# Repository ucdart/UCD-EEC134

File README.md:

EEC 134 Design of High Frequency Systems
======

The EEC 134 course was created to satisfy the need for a senior project course for students who are interested in high freqeuency electronic systems. The two-quarter long course emphasizes on system level design concepts and strives to provide a hands-on experience. As the course evolves, the projects start to encompass many facets of electrical engineering, including system engineering, antenna design, analog circuit design, embedded systems, and digital signal processing. 

The first project option we have implemented is a frequency modulated continuous wave (FMCW) radar system that can perform range, Doppler, and synthetic aperture radar (SAR) measurements. In the first quarter, the students build an FMCW radar system using breadboard and off-the-shelf connectorized RF components. In the second quarter the students focus on improving the system performance and gauge their success by a performance competition. In the future, other project options, such as software-defined radio (SDR), RFID systems, wireless sensors networks, and RF/microwave biomedical systems, will be explored.

<div align="center">
<strong>Watch a live demo at the 2015 Bay Area Maker Faire:</strong><br>

<br>
</div>

----
This Github repo is used to distribute the EEC 134 lecture notes, lab manuals, and supplementary materials such as computer codes with registered EEC 134 students as well as anyone who is interested in the course materials. The public nature of this git repo means that that anyone can contribute to the development of the course materials. Simply create a [pull request](https://help.github.com/articles/using-pull-requests/)

----
Roadmap:
- Lab 1 Baseband circuits
 - add an ADC lab (far future)
 - bring back the function generator
- Lab 2 Amplifier:
 - design a lab for measuring the noise figure
- Lab 3 Oscillator:
 - add a lab on measuring phase noise after we buy new spectrum analyzers
 - add a lab on building a PLL
 - design a lab to demonstrate locking bewteen oscillators. Perhpas with two oscillators and a coupler? 
- Lab 4 Mixer：add modulation to this lab
 - design a lab to demonstrate IQ modulation & demodulation; use an attenuator to show the effect of IQ amplitude imbalance
- Lab 6 convert to a radar only lab 
 - add lab on comparing the sky, sun, and ground noise
- Lab 7 (new) design a comm system only lab
 - 
- PCB tutorial
 - update the screenshots with the OpenGL display option
 - add PCB assembly tutorial
 - add

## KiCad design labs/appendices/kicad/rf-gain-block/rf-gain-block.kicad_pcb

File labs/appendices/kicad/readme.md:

The "short-tline-wrk" is an ADS2013 workspace folder folder that contains the simulation setup and result for short-tline-gamma.pdf

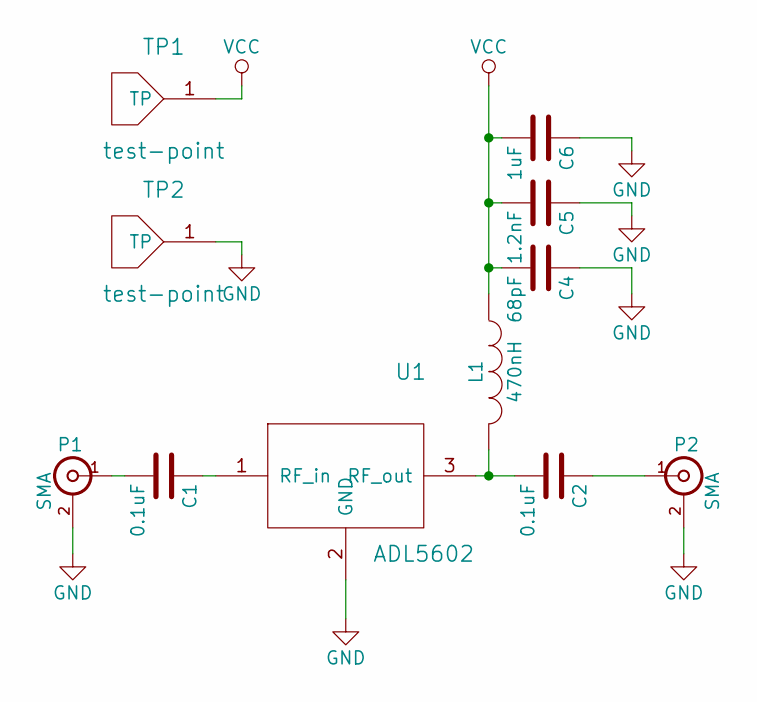
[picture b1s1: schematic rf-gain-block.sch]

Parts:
C1, C2: 0.1uF; smd_0603
C4: 68pF; smd_0603
C5: 1.2nF; smd_0603
C6: 1uF; smd_0603
L1: 470nH; cc_0603ls
P1, P2: SMA
TP1, TP2: test-point; tp
U1: ADL5602; adl5602

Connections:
GND: C4.1, C5.1, C6.1, P1.2 (Ext), P2.2 (Ext), TP2.1, U1.2 (GND)
unnamed: C1.1, U1.1 (RF_in)
unnamed: C1.2, P1.1 (In)
unnamed: C2.1, P2.1 (In)
unnamed: C2.2, L1.2, U1.3 (RF_out)
VCC: C4.2, C5.2, C6.2, L1.1, TP1.1

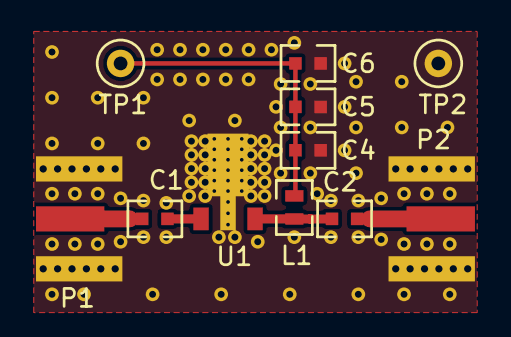
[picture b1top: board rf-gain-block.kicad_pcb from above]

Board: 2 copper layers, 11 parts (0 on the bottom side), 6 nets.

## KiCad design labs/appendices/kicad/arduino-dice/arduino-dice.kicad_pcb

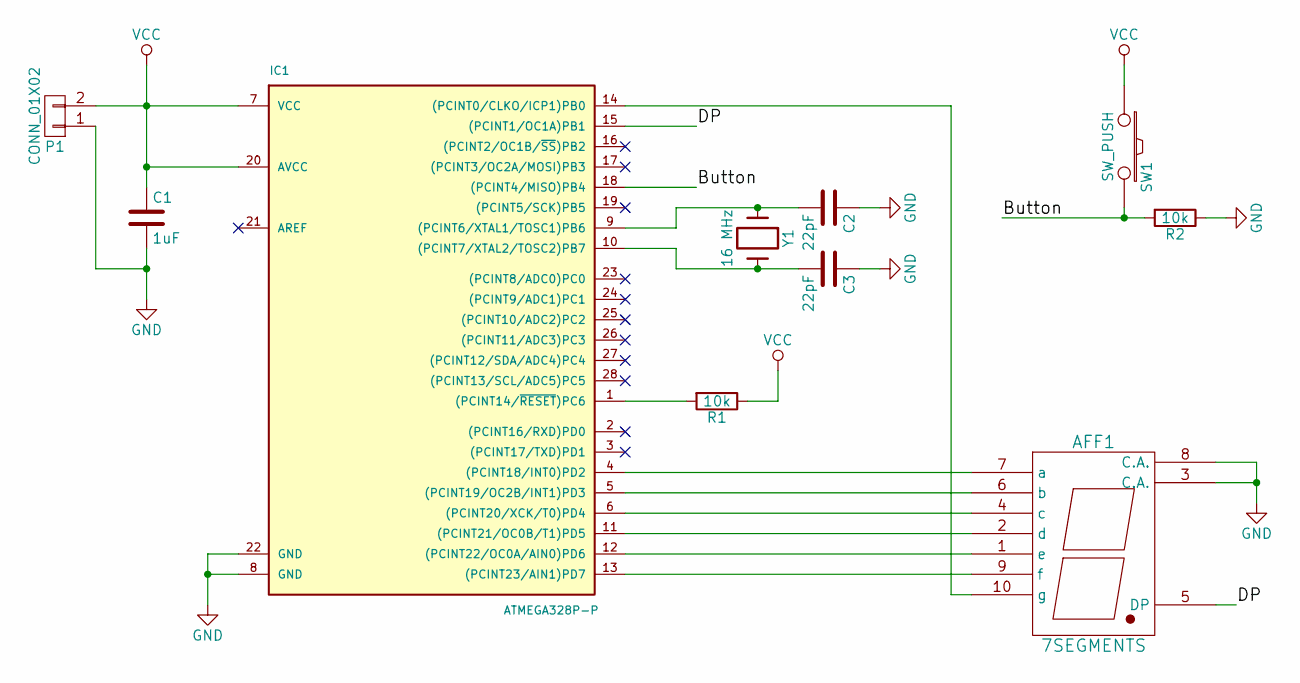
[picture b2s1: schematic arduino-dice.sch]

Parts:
AFF1: 7SEGMENTS; 7segment-hdsp-313e
C1: 1uF; smd_0603
C2, C3: 22pF; smd_0603
IC1: ATMEGA328P-P; atmega328p-pu
P1: CONN_01X02; Pin_Header_Straight_1x02
R1, R2: 10k; smd_0603
SW1: SW_PUSH; sw_push_b3f_1000
Y1: 16 MHz; crystal_hc49us

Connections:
/Button: IC1.18 ((PCINT4/MISO)PB4), R2.2, SW1.2
/DP: AFF1.5 (DP), IC1.15 ((PCINT1/OC1A)PB1)
GND: AFF1.3 (C.A.), AFF1.8 (C.A.), C1.2, C2.1, C3.1, IC1.8 (GND), IC1.22 (GND), P1.1, R2.1
unnamed: AFF1.1 (e), IC1.12 ((PCINT22/OC0A/AIN0)PD6)
unnamed: AFF1.2 (d), IC1.11 ((PCINT21/OC0B/T1)PD5)
unnamed: AFF1.4 (c), IC1.6 ((PCINT20/XCK/T0)PD4)
unnamed: AFF1.6 (b), IC1.5 ((PCINT19/OC2B/INT1)PD3)
unnamed: AFF1.7 (a), IC1.4 ((PCINT18/INT0)PD2)
unnamed: AFF1.9 (f), IC1.13 ((PCINT23/AIN1)PD7)
unnamed: AFF1.10 (g), IC1.14 ((PCINT0/CLKO/ICP1)PB0)
unnamed: C2.2, IC1.9 ((PCINT6/XTAL1/TOSC1)PB6), Y1.1
unnamed: C3.2, IC1.10 ((PCINT7/XTAL2/TOSC2)PB7), Y1.2
unnamed: IC1.1 ((PCINT14/~RESET~)PC6), R1.2
VCC: C1.1, IC1.7 (VCC), IC1.20 (AVCC), P1.2, R1.1, SW1.1

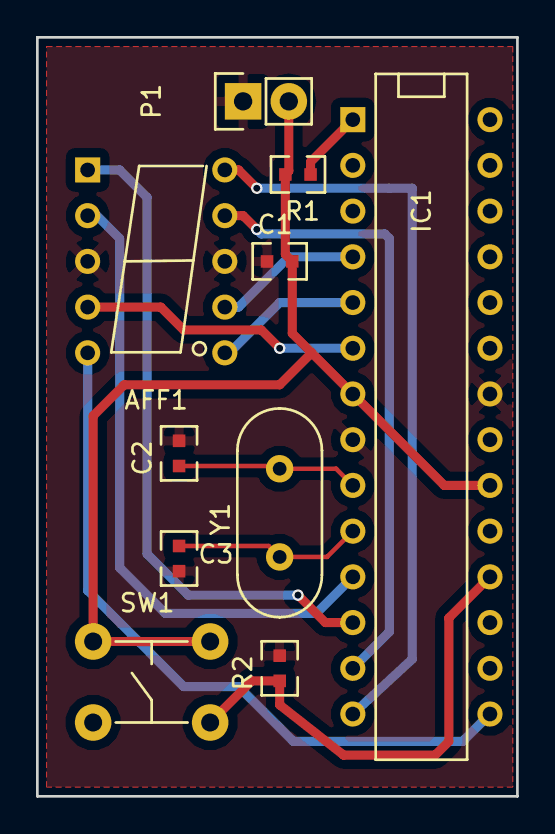
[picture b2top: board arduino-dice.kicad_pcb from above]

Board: 2 copper layers, 26.7 x 42.2 mm, 10 parts (0 on the bottom side), 14 nets.

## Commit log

2014-11-19 Rename Lab-6/radar_range.m to Lab6/radar_range.m
2014-11-19 Rename Lab-6/dbv.m to Lab6/dbv.m
2014-11-19 Rename Lab7/doppler_realtime.m to Lab6/doppler_realtime.m
2014-11-19 Rename Lab7/doppler_realtime_spi_adc.py to Lab6/doppler_realtime_spi_adc.py
2014-11-19 Rename Lab7/doppler_wav.py to Lab6/doppler_wav.py
2014-11-19 Rename Lab7/range_wav.py to Lab6/range_wav.py
2015-01-20 example .wav file
2015-01-20 example .wav file for doppler measurement
2015-06-16 start lab 1
2015-06-18 update lab1
2015-06-19 update lab 1
2015-06-24 update teensy primer
2015-06-24 create new folder for teensy primer
2015-06-24 move code location
2015-08-11 update pcb tutorial
2015-08-15 update, fix schematic corruption
2015-08-22 update lec0
2015-08-23 update rf pcb
2015-08-24 add spectrum analyzer code
2015-08-27 update python processing files
2015-08-28 new code
2015-08-28 update writing
2015-08-30 update lab 1 and schedule
2015-08-30 add radar picture for course introduction
2015-08-30 move location of 24ghz_radar.png
2015-08-30 update pictures
2015-08-30 update images
2015-08-30 update front page figure
2015-08-30 Update LICENSE
2015-08-30 update license information
2015-09-01 update teensy code
2015-09-02 update code
2015-09-03 update sa_teensy code
    spectrum analyzer code now working
    the LCD needs the ST7735 library
    however, the waveform synthesizer doesn't work together with the fft,
    regardless of whether it's 256 or 1024 points.
2015-09-03 update code
    waveform generator and spectrum analyzer now works
2015-09-04 add lab 2
2015-09-04 start lab2
2015-09-04 update lab 2
2015-09-04 picture of spectrum analyzer
2015-09-06 add support documents
2015-09-06 update support documents
2015-09-07 update files
2015-09-08 add lab 5
2015-09-08 update labs
2015-09-09 add back lab 2
2015-09-11 update lab 1 and lecture 0
2015-09-15 update lab 1 -- 3
2015-09-15 update lab 4
2015-09-15 update lab 5
2015-09-15 update schedule
2015-09-15 update labs
2015-09-16 update figure
2015-09-22 update lab manual and appendix
2015-09-22 update lab 2 sma footprint
2015-09-22 upload lecture notes
2015-09-23 update KiCad tutorial
2015-09-24 update checklist and lec0
2015-09-29 update pcb
2015-10-06 update lec1
2015-10-09 update lec3
2015-10-09 update lec 2 and 3
2015-10-11 update python code to avoid divide by zero
2015-10-17 correct typos
2015-10-26 update pcb review guideline
2015-11-06 add lec 7
2015-11-13 update lec8
2015-11-13 update lec6
2015-11-14 update lecture 6 & 7
2015-11-14 update lec7
2015-11-15 test branch
2015-11-18 update lab 6
2015-11-19 update lab6
2015-11-20 add system lectures
2015-11-20 update lab 6 and lecture notes
2015-11-24 upload q2 project guidelines
2015-11-24 update lectures
2015-11-25 update q2 guidelines
2015-12-30 bug fix
    corrected the bug that prevents processing large files
2016-09-23 update lab manual
2016-09-23 update various files for 2016
2016-09-23 update 2016 materials
2016-09-23 update lecture 0
2016-09-24 update TA office hours
2016-09-25 correct a typo in Lab 1
2016-09-26 update office hours
2016-09-30 correct figure numbers
2016-10-19 update lecture 3
2016-10-20 update lab 2 and lecture 4
2016-10-22 update lab 1 & 2
2016-11-16 updat lab 5
2017-02-14 update quarter 2 guideline
2017-03-21 update lab6 code
2017-10-21 update lab manuals
2017-10-21 update lab3
2018-10-20 update lec5
2018-12-03 update lab 6 code
    added code for using the Analog Discovery and CSV files
2019-01-12 update quarter 2 guidelines
2020-02-06 udpate labs for 2020
2020-02-22 update lab 5 and 6
